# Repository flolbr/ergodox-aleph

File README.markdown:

# Ergodox Aleph 1

Please note that this project uses the nightly version of KiCad (or Kicad 6).

Ergodox [Aleph 1][aleph] is a modification of the [Ergodox Infinity][original].

Major changes include:

* Full Under-Key RGB
* Through-hole diodes for easy soldering
* Replaced the expensive J-Link Needle port with a cheaper J-Link socket
* RGB header for optional underglow
* Added stabiliser holes to 2U keys on thumb cluster
* Replaced discontinued USB ports with new parts

**I've only done the left board so far.**

[aleph]: https://en.wikipedia.org/wiki/Aleph_number
[original]: https://input.club/devices/infinity-ergodox/

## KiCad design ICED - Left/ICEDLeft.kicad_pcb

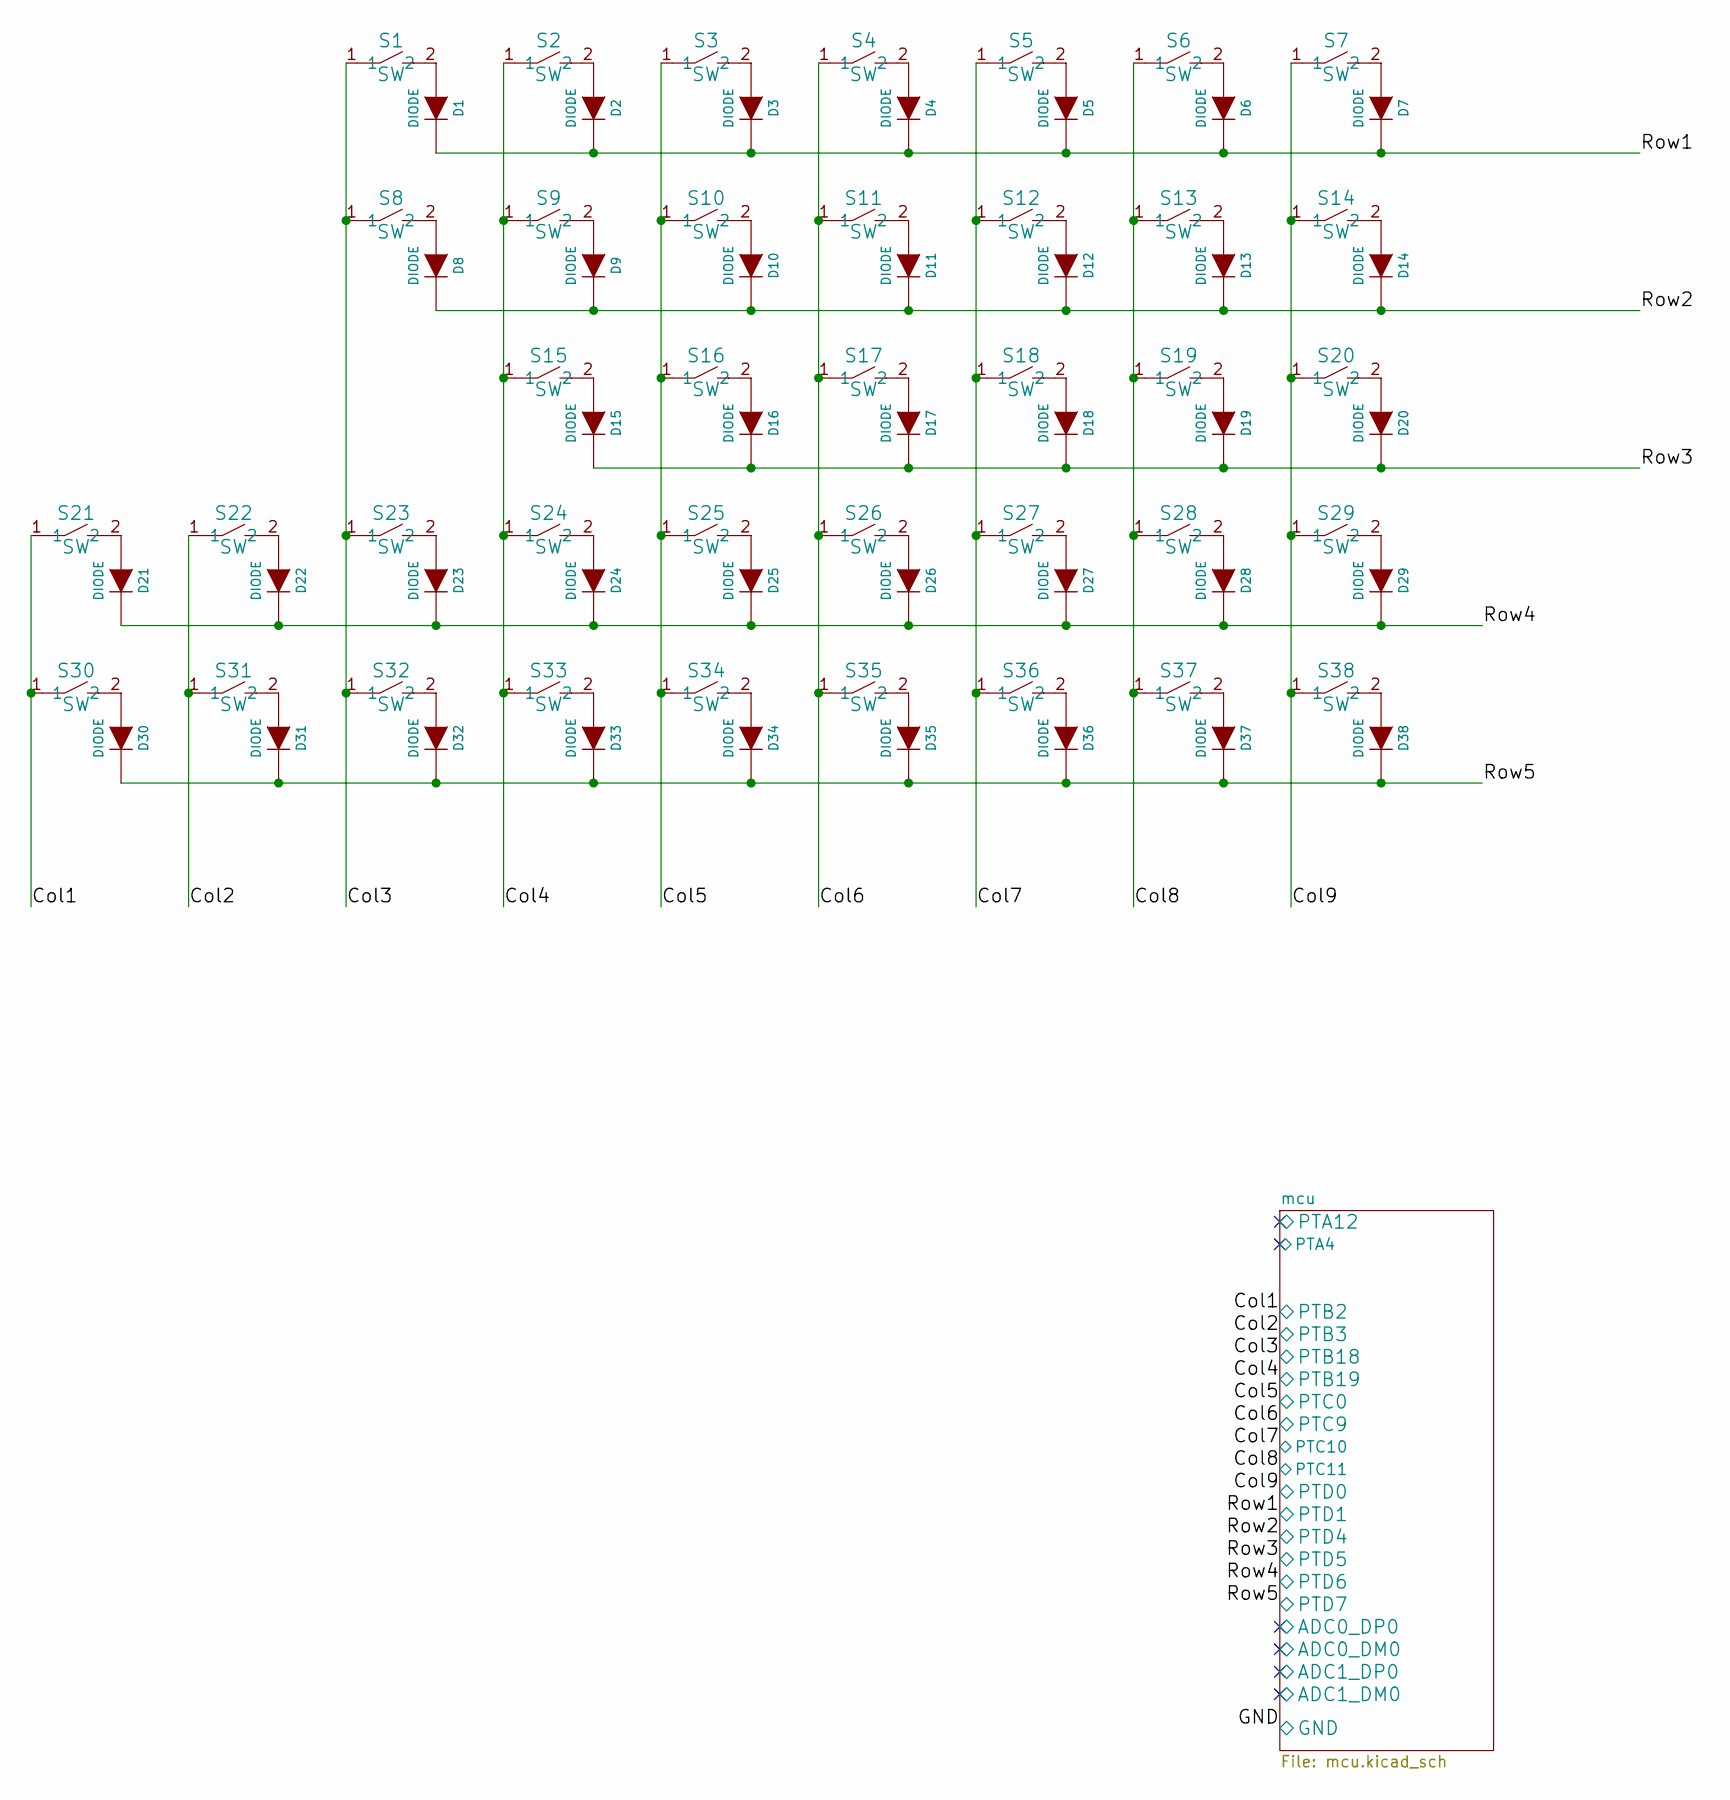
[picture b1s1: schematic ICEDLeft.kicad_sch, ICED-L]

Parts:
D1, D2, D3, D4, D5, D6, D7, D8, D9, D10, D11, D12, D13, D14, D15, D16, D17, D18, D19, D20, D21, D22, D23, D24, D25, D26, D27, D28, D29, D30, D31, D32, D33, D34, D35, D36, D37, D38: DIODE; SOT123-DIODE
S1, S2, S3, S4, S5, S6, S7, S8, S9, S10, S11, S12, S13, S14, S15, S16, S17, S18, S19, S20, S21, S22, S23, S24, S25, S26, S27, S28, S29, S30, S31, S32, S33, S34, S35, S36, S37, S38: SW; SW_Hotswap_Kailh

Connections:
/Col1: S21.1, S30.1; also elsewhere on the board
/Col2: S22.1, S31.1; also elsewhere on the board
/Col3: S1.1, S8.1, S23.1, S32.1; also elsewhere on the board
/Col4: S2.1, S9.1, S15.1, S24.1, S33.1; also elsewhere on the board
/Col5: S3.1, S10.1, S16.1, S25.1, S34.1; also elsewhere on the board
/Col6: S4.1, S11.1, S17.1, S26.1, S35.1; also elsewhere on the board
/Col7: S5.1, S12.1, S18.1, S27.1, S36.1; also elsewhere on the board
/Col8: S6.1, S13.1, S19.1, S28.1, S37.1; also elsewhere on the board
/Col9: S7.1, S14.1, S20.1, S29.1, S38.1; also elsewhere on the board
/Row1: D1.2 (K), D2.2 (K), D3.2 (K), D4.2 (K), D5.2 (K), D6.2 (K), D7.2 (K); also elsewhere on the board
/Row2: D8.2 (K), D9.2 (K), D10.2 (K), D11.2 (K), D12.2 (K), D13.2 (K), D14.2 (K); also elsewhere on the board
/Row3: D15.2 (K), D16.2 (K), D17.2 (K), D18.2 (K), D19.2 (K), D20.2 (K); also elsewhere on the board
/Row4: D21.2 (K), D22.2 (K), D23.2 (K), D24.2 (K), D25.2 (K), D26.2 (K), D27.2 (K), D28.2 (K), D29.2 (K); also elsewhere on the board
/Row5: D30.2 (K), D31.2 (K), D32.2 (K), D33.2 (K), D34.2 (K), D35.2 (K), D36.2 (K), D37.2 (K), D38.2 (K); also elsewhere on the board
unnamed: D1.1 (A), S1.2
unnamed: D2.1 (A), S2.2
unnamed: D3.1 (A), S3.2
unnamed: D4.1 (A), S4.2
unnamed: D5.1 (A), S5.2
unnamed: D6.1 (A), S6.2
unnamed: D7.1 (A), S7.2
unnamed: D8.1 (A), S8.2
unnamed: D9.1 (A), S9.2
unnamed: D10.1 (A), S10.2
unnamed: D11.1 (A), S11.2
unnamed: D12.1 (A), S12.2
unnamed: D13.1 (A), S13.2
unnamed: D14.1 (A), S14.2
unnamed: D15.1 (A), S15.2
unnamed: D16.1 (A), S16.2
unnamed: D17.1 (A), S17.2
unnamed: D18.1 (A), S18.2
unnamed: D19.1 (A), S19.2
unnamed: D20.1 (A), S20.2
unnamed: D21.1 (A), S21.2
unnamed: D22.1 (A), S22.2
unnamed: D23.1 (A), S23.2
unnamed: D24.1 (A), S24.2
unnamed: D25.1 (A), S25.2
unnamed: D26.1 (A), S26.2
unnamed: D27.1 (A), S27.2
unnamed: D28.1 (A), S28.2
unnamed: D29.1 (A), S29.2
unnamed: D30.1 (A), S30.2
unnamed: D31.1 (A), S31.2
unnamed: D32.1 (A), S32.2
unnamed: D33.1 (A), S33.2
unnamed: D34.1 (A), S34.2
unnamed: D35.1 (A), S35.2
unnamed: D36.1 (A), S36.2
unnamed: D37.1 (A), S37.2
unnamed: D38.1 (A), S38.2

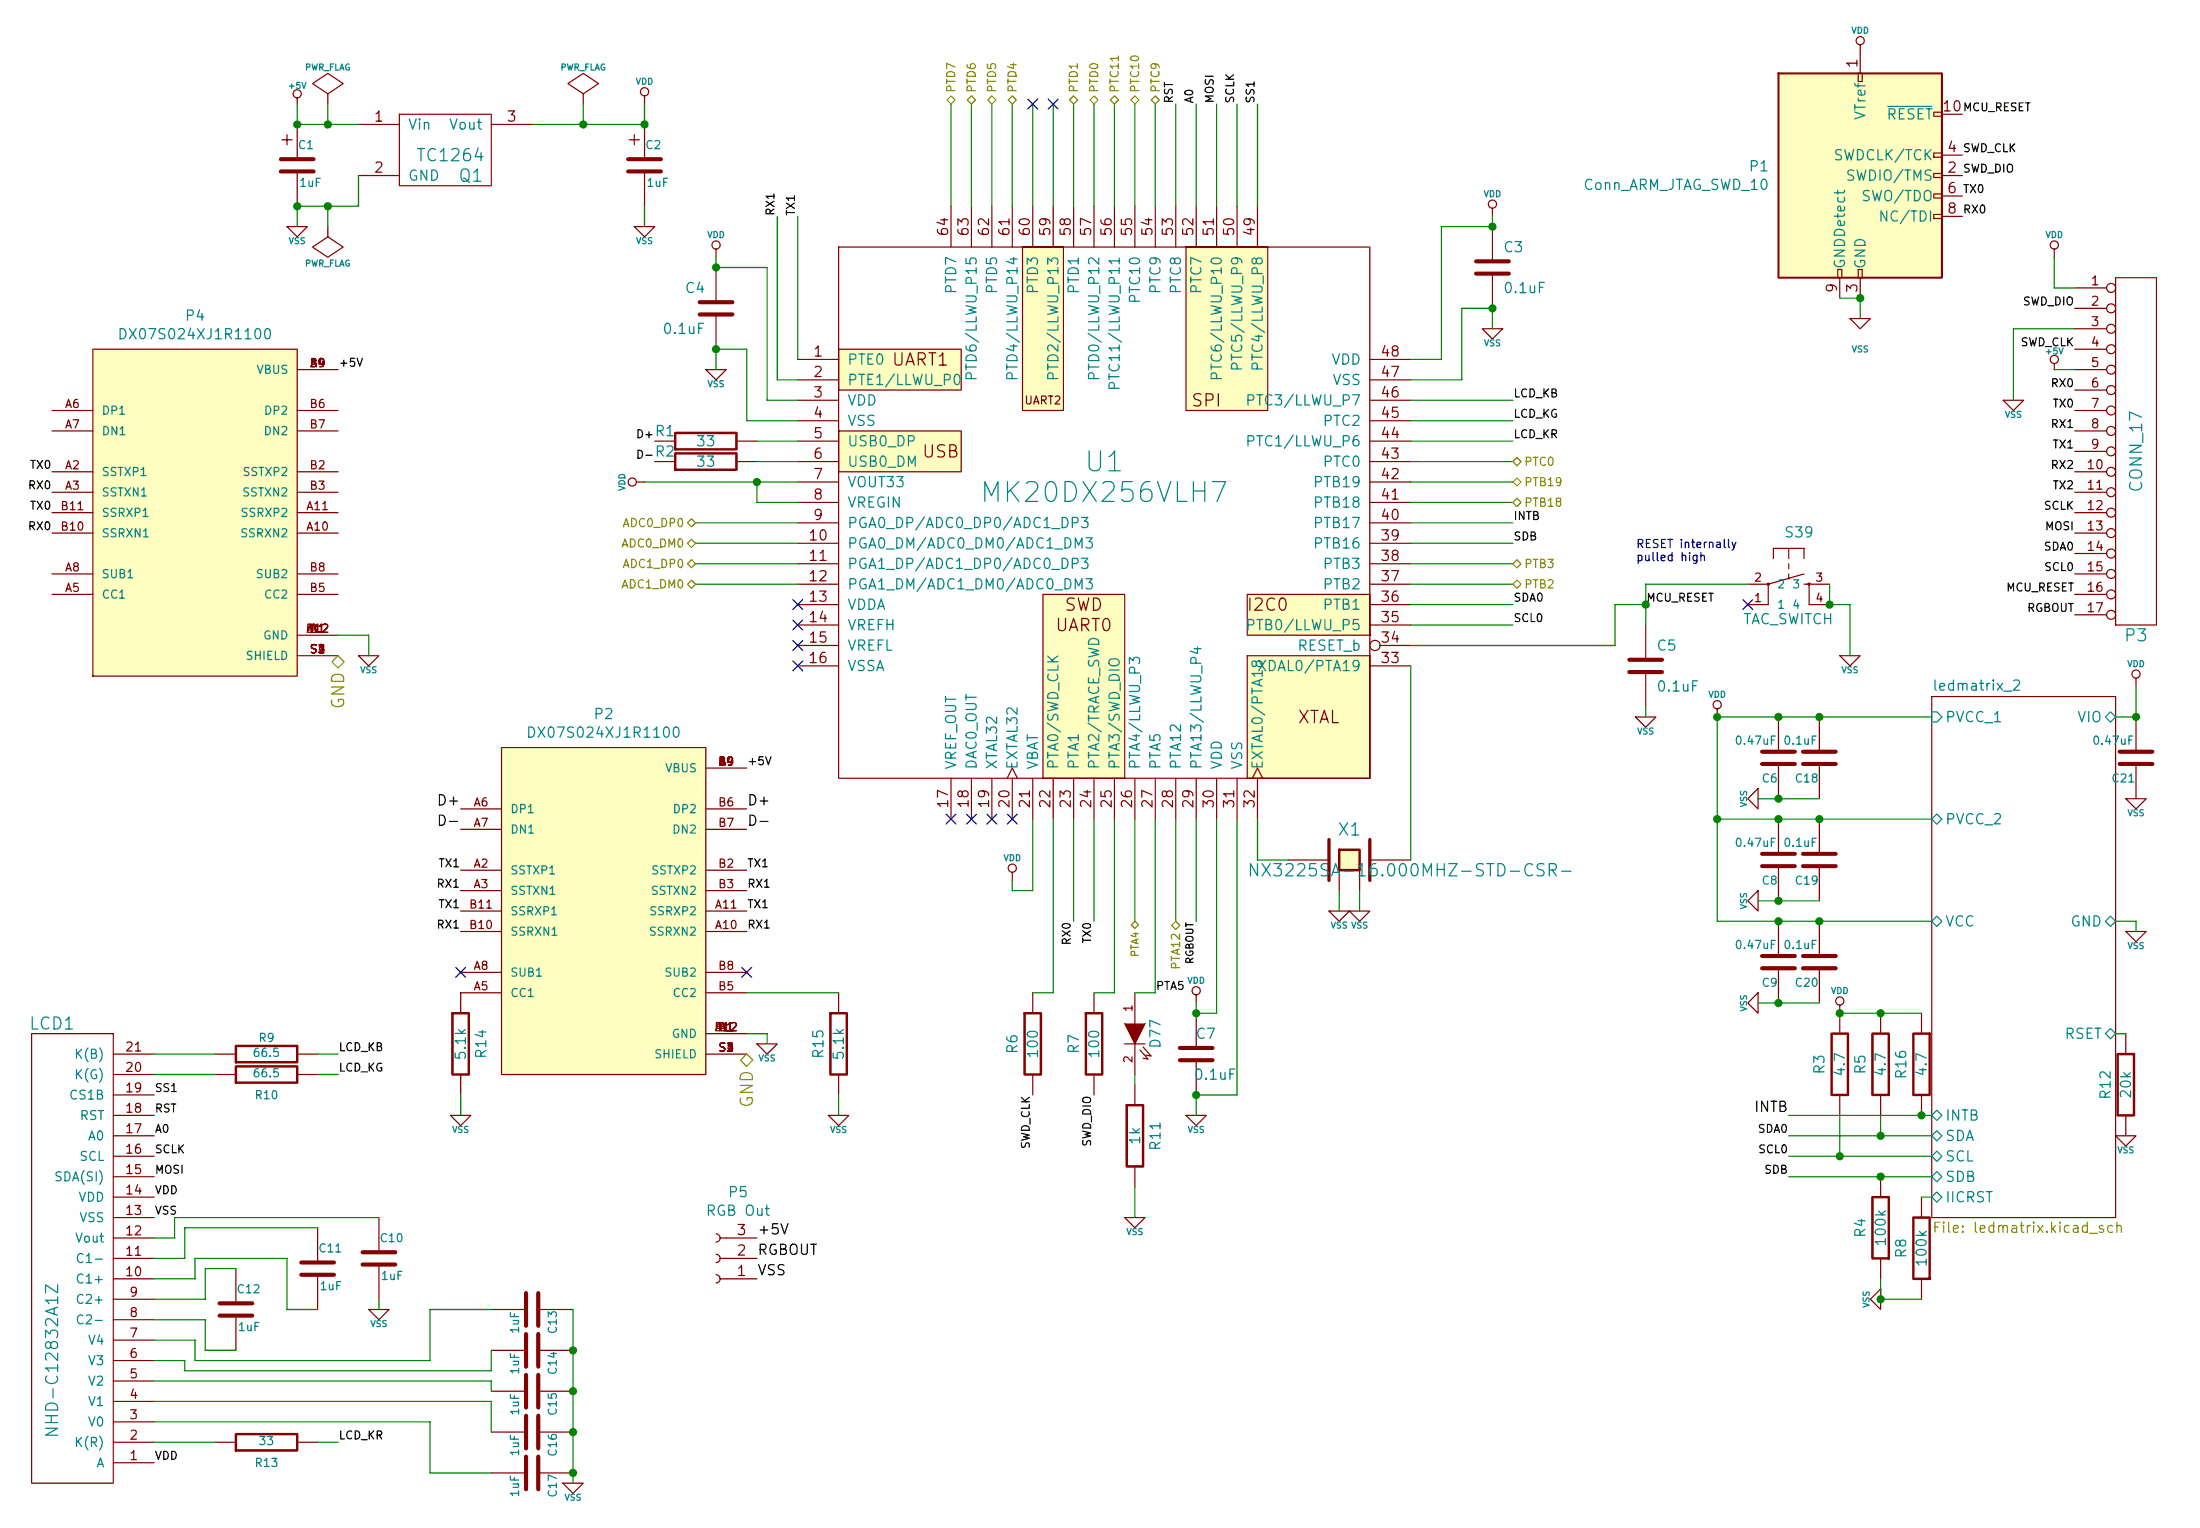
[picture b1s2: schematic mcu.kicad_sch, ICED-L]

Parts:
C1, C2, C10, C11, C12, C13, C14, C15, C16, C17: 1uF; SMD-1005
C3, C4, C5, C7, C18, C19, C20: 0.1uF; SMD-1005
C6, C8, C9, C21: 0.47uF; SMD-1005
D77: LED; LED-0603
LCD1: NHD-C12832A1Z
P1: Conn_ARM_JTAG_SWD_10; SHF-105-01-L-D-TH
P2, P4: DX07S024XJ1R1100; JAE_DX07S024XJ1R1100; PARTREV 1
P3: CONN_17; HEADER_1x17
P5: RGB Out; PinHeader_1x03_P2.54mm_Horizontal
Q1: TC1264; SOT-223
R1, R2, R13: 33; SMD-1005
R3, R5, R16: 4.7; SMD-1005
R4, R8: 100k; SMD-1005
R6, R7: 100; SMD-1005
R9, R10: 66.5; SMD-1005
R11: 1k; SMD-1005
R12: 20k; SMD-1005
R14, R15: 5.1k; SMD-1005
S39: TAC_SWITCH; TACT_5.2x5.2
U1: MK20DX256VLH7; LQFP64
X1: NX3225SA-16.000MHZ-STD-CSR-; NX3225SA

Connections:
+5V: C1.1, P2.A4 (VBUS), P2.A9 (VBUS), P2.B4 (VBUS), P2.B9 (VBUS), P3.5, P4.A4 (VBUS), P4.A9 (VBUS), P4.B4 (VBUS), P4.B9 (VBUS), P5.3, Q1.1 (Vin)
/Col1: U1.37 (PTB2); also elsewhere on the board
/Col2: U1.38 (PTB3); also elsewhere on the board
/Col3: U1.41 (PTB18); also elsewhere on the board
/Col4: U1.42 (PTB19); also elsewhere on the board
/Col5: U1.43 (PTC0); also elsewhere on the board
/Col6: U1.54 (PTC9); also elsewhere on the board
/Col7: U1.55 (PTC10); also elsewhere on the board
/Col8: U1.56 (PTC11/LLWU_P11); also elsewhere on the board
/Col9: U1.57 (PTD0/LLWU_P12); also elsewhere on the board
/GND: P2.S1 (SHIELD), P2.S2 (SHIELD), P2.S3 (SHIELD), P2.S4 (SHIELD), P4.S1 (SHIELD), P4.S2 (SHIELD), P4.S3 (SHIELD), P4.S4 (SHIELD)
/Row1: U1.58 (PTD1); also elsewhere on the board
/Row2: U1.61 (PTD4/LLWU_P14); also elsewhere on the board
/Row3: U1.62 (PTD5); also elsewhere on the board
/Row4: U1.63 (PTD6/LLWU_P15); also elsewhere on the board
/Row5: U1.64 (PTD7); also elsewhere on the board
/mcu/A0: LCD1.17 (A0), U1.52 (PTC7)
/mcu/ADC0_DM0: U1.10 (PGA0_DM/ADC0_DM0/ADC1_DM3)
/mcu/ADC0_DP0: U1.9 (PGA0_DP/ADC0_DP0/ADC1_DP3)
/mcu/ADC1_DM0: U1.12 (PGA1_DM/ADC1_DM0/ADC0_DM3)
/mcu/ADC1_DP0: U1.11 (PGA1_DP/ADC1_DP0/ADC0_DP3)
/mcu/D+: P2.A6 (DP1), P2.B6 (DP2), R1.1
/mcu/D-: P2.A7 (DN1), P2.B7 (DN2), R2.1
/mcu/INTB: R16.2, U1.40 (PTB17); also elsewhere on the board
/mcu/LCD_KB: R9.2, U1.46 (PTC3/LLWU_P7)
/mcu/LCD_KG: R10.2, U1.45 (PTC2)
/mcu/LCD_KR: R13.2, U1.44 (PTC1/LLWU_P6)
/mcu/MCU_RESET: C5.1, P1.10 (~RESET), P3.16, S39.2, U1.34 (RESET_b)
/mcu/MOSI: LCD1.15 (SDA(SI)), P3.13, U1.51 (PTC6/LLWU_P10)
/mcu/PTA4: U1.26 (PTA4/LLWU_P3)
/mcu/PTA5: D77.1 (A), U1.27 (PTA5)
/mcu/PTA12: U1.28 (PTA12)
/mcu/RGBOUT: P3.17, P5.2, U1.29 (PTA13/LLWU_P4)
/mcu/RST: LCD1.18 (RST), U1.53 (PTC8)
/mcu/RX0: P1.8 (NC/TDI), P3.6, P4.A3 (SSTXN1), P4.B10 (SSRXN1), U1.23 (PTA1)
/mcu/RX1: P2.A3 (SSTXN1), P2.A10 (SSRXN2), P2.B3 (SSTXN2), P2.B10 (SSRXN1), P3.8, U1.2 (PTE1/LLWU_P0)
/mcu/RX2: P3.10
/mcu/SCL0: P3.15, R3.1, U1.35 (PTB0/LLWU_P5); also elsewhere on the board
/mcu/SCLK: LCD1.16 (SCL), P3.12, U1.50 (PTC5/LLWU_P9)
/mcu/SDA0: P3.14, R5.1, U1.36 (PTB1); also elsewhere on the board
/mcu/SDB: R4.2, U1.39 (PTB16); also elsewhere on the board
/mcu/SS1: LCD1.19 (CS1B), U1.49 (PTC4/LLWU_P8)
/mcu/SWD_CLK: P1.4 (SWDCLK/TCK), P3.4, R6.2
/mcu/SWD_DIO: P1.2 (SWDIO/TMS), P3.2, R7.2
/mcu/TX0: P1.6 (SWO/TDO), P3.7, P4.A2 (SSTXP1), P4.B11 (SSRXP1), U1.24 (PTA2/TRACE_SWD)
/mcu/TX1: P2.A2 (SSTXP1), P2.A11 (SSRXP2), P2.B2 (SSTXP2), P2.B11 (SSRXP1), P3.9, U1.1 (PTE0)
/mcu/TX2: P3.11
/mcu/ledmatrix_2/IICRST: R8.2; also elsewhere on the board
/mcu/ledmatrix_2/RSET: R12.1; also elsewhere on the board
unnamed: C10.1, LCD1.12 (Vout)
unnamed: C11.1, LCD1.11 (C1-)
unnamed: C11.2, LCD1.10 (C1+)
unnamed: C12.1, LCD1.9 (C2+)
unnamed: C12.2, LCD1.8 (C2-)
unnamed: C13.2, LCD1.7 (V4)
unnamed: C14.2, LCD1.6 (V3)
unnamed: C15.2, LCD1.5 (V2)
unnamed: C16.2, LCD1.4 (V1)
unnamed: C17.2, LCD1.3 (V0)
unnamed: D77.2 (K), R11.1
unnamed: LCD1.2 (K(R)), R13.1
unnamed: LCD1.20 (K(G)), R10.1
unnamed: LCD1.21 (K(B)), R9.1
unnamed: R1.2, U1.5 (USB0_DP)
unnamed: R2.2, U1.6 (USB0_DM)
unnamed: R6.1, U1.22 (PTA0/SWD_CLK)
unnamed: R7.1, U1.25 (PTA3/SWD_DIO)
unnamed: P2.A5 (CC1), R14.1
unnamed: P2.B5 (CC2), R15.1
unnamed: U1.32 (EXTAL0/PTA18), X1.1
unnamed: U1.33 (XDAL0/PTA19), X1.3
VDD: C2.1, C3.1, C4.1, C6.2, C7.1, C8.2, C9.2, C18.2, C19.2, C20.2, C21.2, LCD1.1 (A), LCD1.14 (VDD), P1.1 (VTref), P3.1, Q1.3 (Vout), R3.2, R5.2, R16.1, U1.3 (VDD), U1.7 (VOUT33), U1.8 (VREGIN), U1.21 (VBAT), U1.30 (VDD), U1.48 (VDD); also elsewhere on the board
VSS: C1.2, C2.2, C3.2, C4.2, C5.2, C6.1, C7.2, C8.1, C9.1, C10.2, C13.1, C14.1, C15.1, C16.1, C17.1, C18.1, C19.1, C20.1, C21.1, LCD1.13 (VSS), P1.3 (GND), P1.5 (GND), P1.9 (GNDDetect), P2.A1 (GND), P2.A12 (GND), P2.B1 (GND), P2.B12 (GND), P3.3, P4.A1 (GND), P4.A12 (GND), P4.B1 (GND), P4.B12 (GND), P5.1, Q1.2 (GND), R4.1, R8.1, R11.2, R12.2, R14.2, R15.2, S39.3, S39.4, U1.4 (VSS), U1.31 (VSS), U1.47 (VSS), X1.2, X1.4; also elsewhere on the board

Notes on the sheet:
RESET internally pulled high

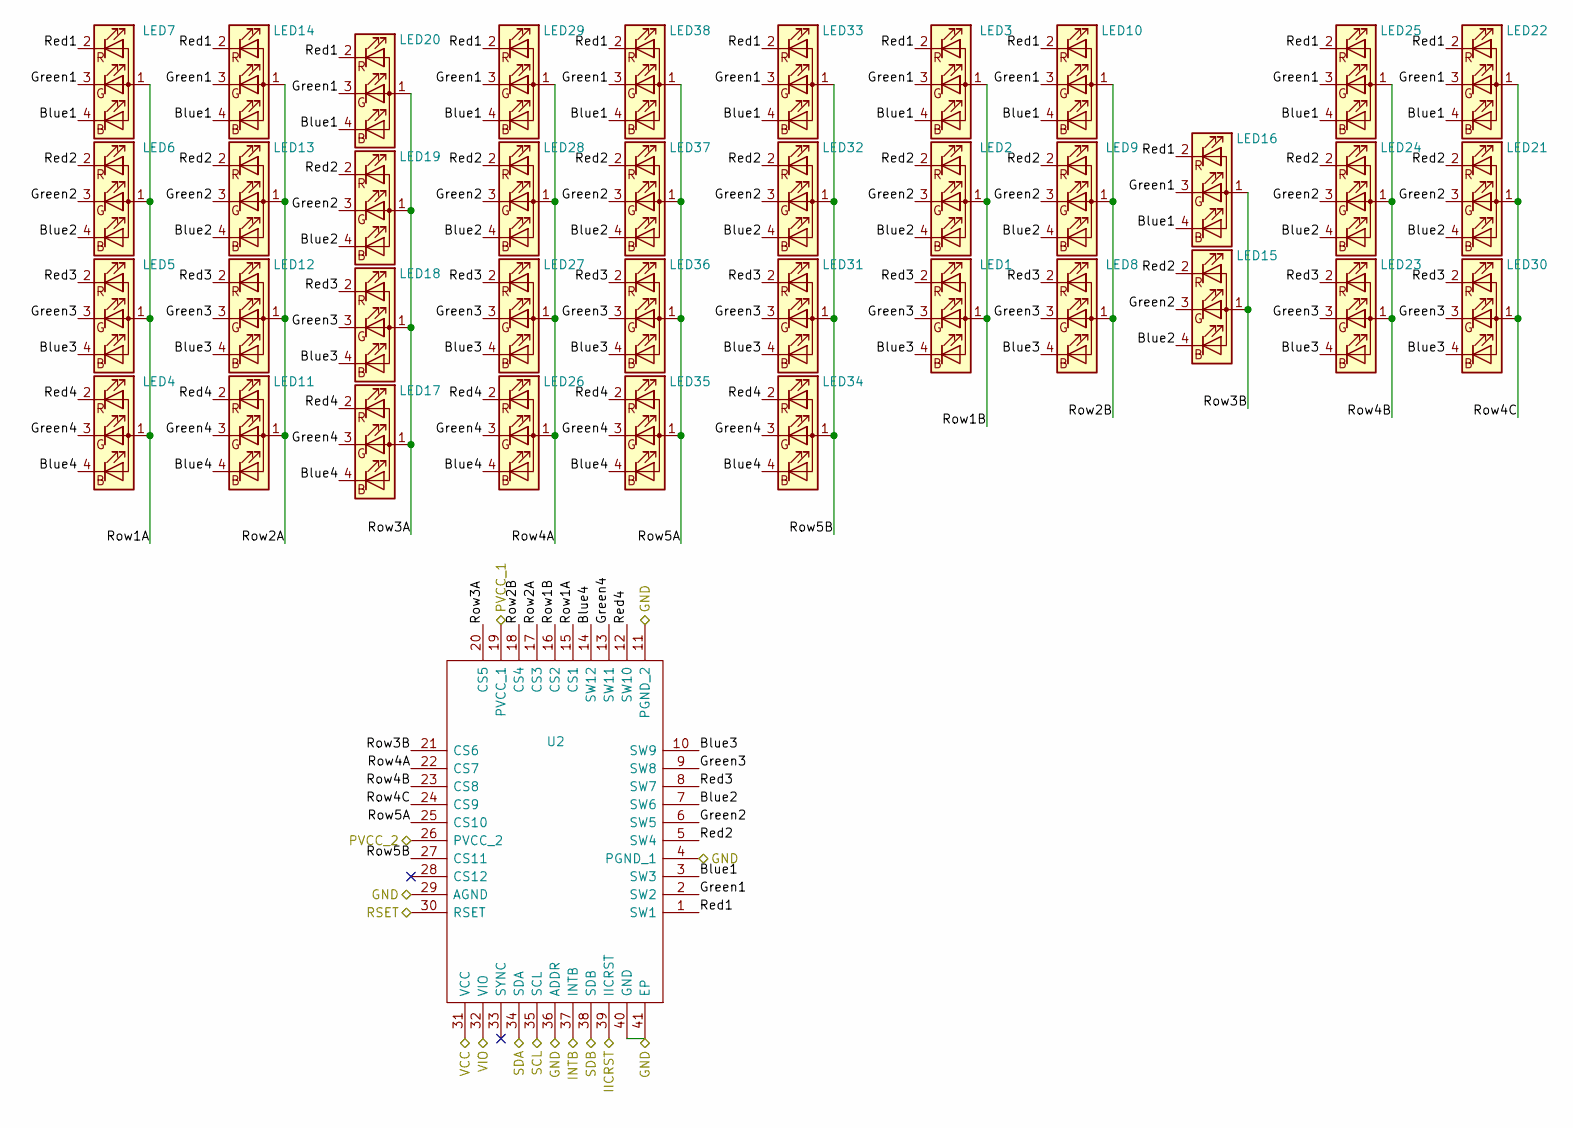
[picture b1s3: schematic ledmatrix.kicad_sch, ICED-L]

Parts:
LED1, LED2, LED3, LED4, LED5, LED6, LED7, LED8, LED9, LED10, LED11, LED12, LED13, LED14, LED15, LED16, LED17, LED18, LED19, LED20, LED21, LED22, LED23, LED24, LED25, LED26, LED27, LED28, LED29, LED30, LED31, LED32, LED33, LED34, LED35, LED36, LED37, LED38: RGB_0606; 0606
U2: IS31FL3737-QFLS4-TR; QFN40P500X500X80-41N-D; Manufacturer_Part_Number IS31FL3737-QFLS4-TR; Mouser Part Number 870-31FL3737QFLS4TR

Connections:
/mcu/INTB: U2.37 (INTB); also elsewhere on the board
/mcu/SCL0: U2.35 (SCL); also elsewhere on the board
/mcu/SDA0: U2.34 (SDA); also elsewhere on the board
/mcu/SDB: U2.38 (SDB); also elsewhere on the board
/mcu/ledmatrix_2/Blue1: LED3.4 (BK), LED7.4 (BK), LED10.4 (BK), LED14.4 (BK), LED16.4 (BK), LED20.4 (BK), LED22.4 (BK), LED25.4 (BK), LED29.4 (BK), LED33.4 (BK), LED38.4 (BK), U2.3 (SW3)
/mcu/ledmatrix_2/Blue2: LED2.4 (BK), LED6.4 (BK), LED9.4 (BK), LED13.4 (BK), LED15.4 (BK), LED19.4 (BK), LED21.4 (BK), LED24.4 (BK), LED28.4 (BK), LED32.4 (BK), LED37.4 (BK), U2.7 (SW6)
/mcu/ledmatrix_2/Blue3: LED1.4 (BK), LED5.4 (BK), LED8.4 (BK), LED12.4 (BK), LED18.4 (BK), LED23.4 (BK), LED27.4 (BK), LED30.4 (BK), LED31.4 (BK), LED36.4 (BK), U2.10 (SW9)
/mcu/ledmatrix_2/Blue4: LED4.4 (BK), LED11.4 (BK), LED17.4 (BK), LED26.4 (BK), LED34.4 (BK), LED35.4 (BK), U2.14 (SW12)
/mcu/ledmatrix_2/Green1: LED3.3 (GK), LED7.3 (GK), LED10.3 (GK), LED14.3 (GK), LED16.3 (GK), LED20.3 (GK), LED22.3 (GK), LED25.3 (GK), LED29.3 (GK), LED33.3 (GK), LED38.3 (GK), U2.2 (SW2)
/mcu/ledmatrix_2/Green2: LED2.3 (GK), LED6.3 (GK), LED9.3 (GK), LED13.3 (GK), LED15.3 (GK), LED19.3 (GK), LED21.3 (GK), LED24.3 (GK), LED28.3 (GK), LED32.3 (GK), LED37.3 (GK), U2.6 (SW5)
/mcu/ledmatrix_2/Green3: LED1.3 (GK), LED5.3 (GK), LED8.3 (GK), LED12.3 (GK), LED18.3 (GK), LED23.3 (GK), LED27.3 (GK), LED30.3 (GK), LED31.3 (GK), LED36.3 (GK), U2.9 (SW8)
/mcu/ledmatrix_2/Green4: LED4.3 (GK), LED11.3 (GK), LED17.3 (GK), LED26.3 (GK), LED34.3 (GK), LED35.3 (GK), U2.13 (SW11)
/mcu/ledmatrix_2/IICRST: U2.39 (IICRST); also elsewhere on the board
/mcu/ledmatrix_2/RSET: U2.30 (RSET); also elsewhere on the board
/mcu/ledmatrix_2/Red1: LED3.2 (RK), LED7.2 (RK), LED10.2 (RK), LED14.2 (RK), LED16.2 (RK), LED20.2 (RK), LED22.2 (RK), LED25.2 (RK), LED29.2 (RK), LED33.2 (RK), LED38.2 (RK), U2.1 (SW1)
/mcu/ledmatrix_2/Red2: LED2.2 (RK), LED6.2 (RK), LED9.2 (RK), LED13.2 (RK), LED15.2 (RK), LED19.2 (RK), LED21.2 (RK), LED24.2 (RK), LED28.2 (RK), LED32.2 (RK), LED37.2 (RK), U2.5 (SW4)
/mcu/ledmatrix_2/Red3: LED1.2 (RK), LED5.2 (RK), LED8.2 (RK), LED12.2 (RK), LED18.2 (RK), LED23.2 (RK), LED27.2 (RK), LED30.2 (RK), LED31.2 (RK), LED36.2 (RK), U2.8 (SW7)
/mcu/ledmatrix_2/Red4: LED4.2 (RK), LED11.2 (RK), LED17.2 (RK), LED26.2 (RK), LED34.2 (RK), LED35.2 (RK), U2.12 (SW10)
/mcu/ledmatrix_2/Row1A: LED4.1 (A), LED5.1 (A), LED6.1 (A), LED7.1 (A), U2.15 (CS1)
/mcu/ledmatrix_2/Row1B: LED1.1 (A), LED2.1 (A), LED3.1 (A), U2.16 (CS2)
/mcu/ledmatrix_2/Row2A: LED11.1 (A), LED12.1 (A), LED13.1 (A), LED14.1 (A), U2.17 (CS3)
/mcu/ledmatrix_2/Row2B: LED8.1 (A), LED9.1 (A), LED10.1 (A), U2.18 (CS4)
/mcu/ledmatrix_2/Row3A: LED17.1 (A), LED18.1 (A), LED19.1 (A), LED20.1 (A), U2.20 (CS5)
/mcu/ledmatrix_2/Row3B: LED15.1 (A), LED16.1 (A), U2.21 (CS6)
/mcu/ledmatrix_2/Row4A: LED26.1 (A), LED27.1 (A), LED28.1 (A), LED29.1 (A), U2.22 (CS7)
/mcu/ledmatrix_2/Row4B: LED23.1 (A), LED24.1 (A), LED25.1 (A), U2.23 (CS8)
/mcu/ledmatrix_2/Row4C: LED21.1 (A), LED22.1 (A), LED30.1 (A), U2.24 (CS9)
/mcu/ledmatrix_2/Row5A: LED35.1 (A), LED36.1 (A), LED37.1 (A), LED38.1 (A), U2.25 (CS10)
/mcu/ledmatrix_2/Row5B: LED31.1 (A), LED32.1 (A), LED33.1 (A), LED34.1 (A), U2.27 (CS11)
VDD: U2.19 (PVCC_1), U2.26 (PVCC_2), U2.31 (VCC), U2.32 (VIO); also elsewhere on the board
VSS: U2.4 (PGND_1), U2.11 (PGND_2), U2.29 (AGND), U2.36 (ADDR), U2.40 (GND), U2.41 (EP); also elsewhere on the board

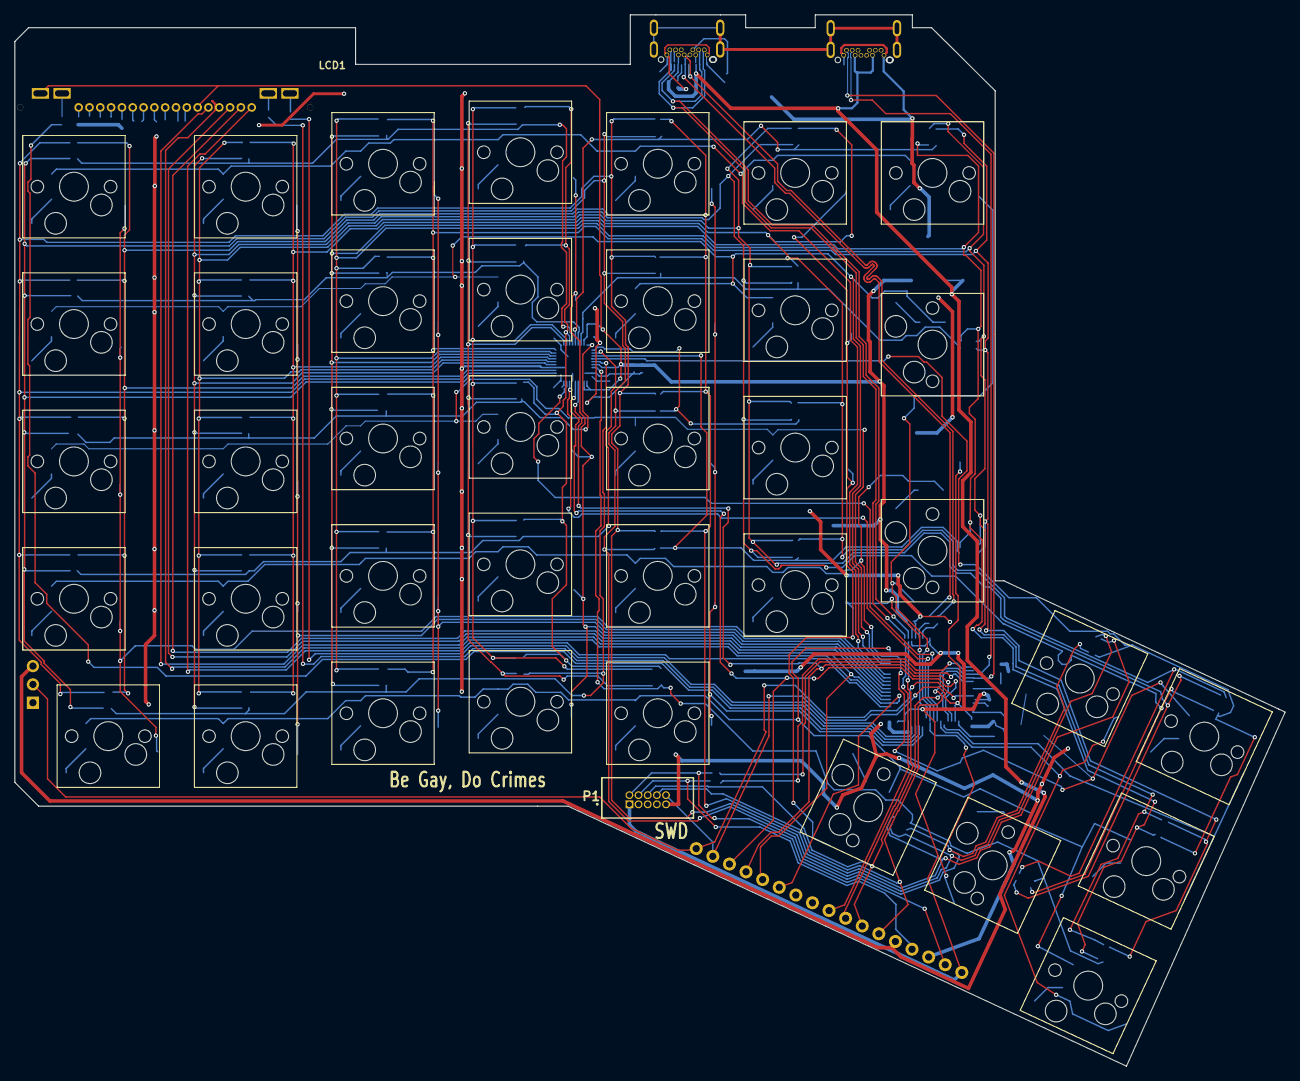
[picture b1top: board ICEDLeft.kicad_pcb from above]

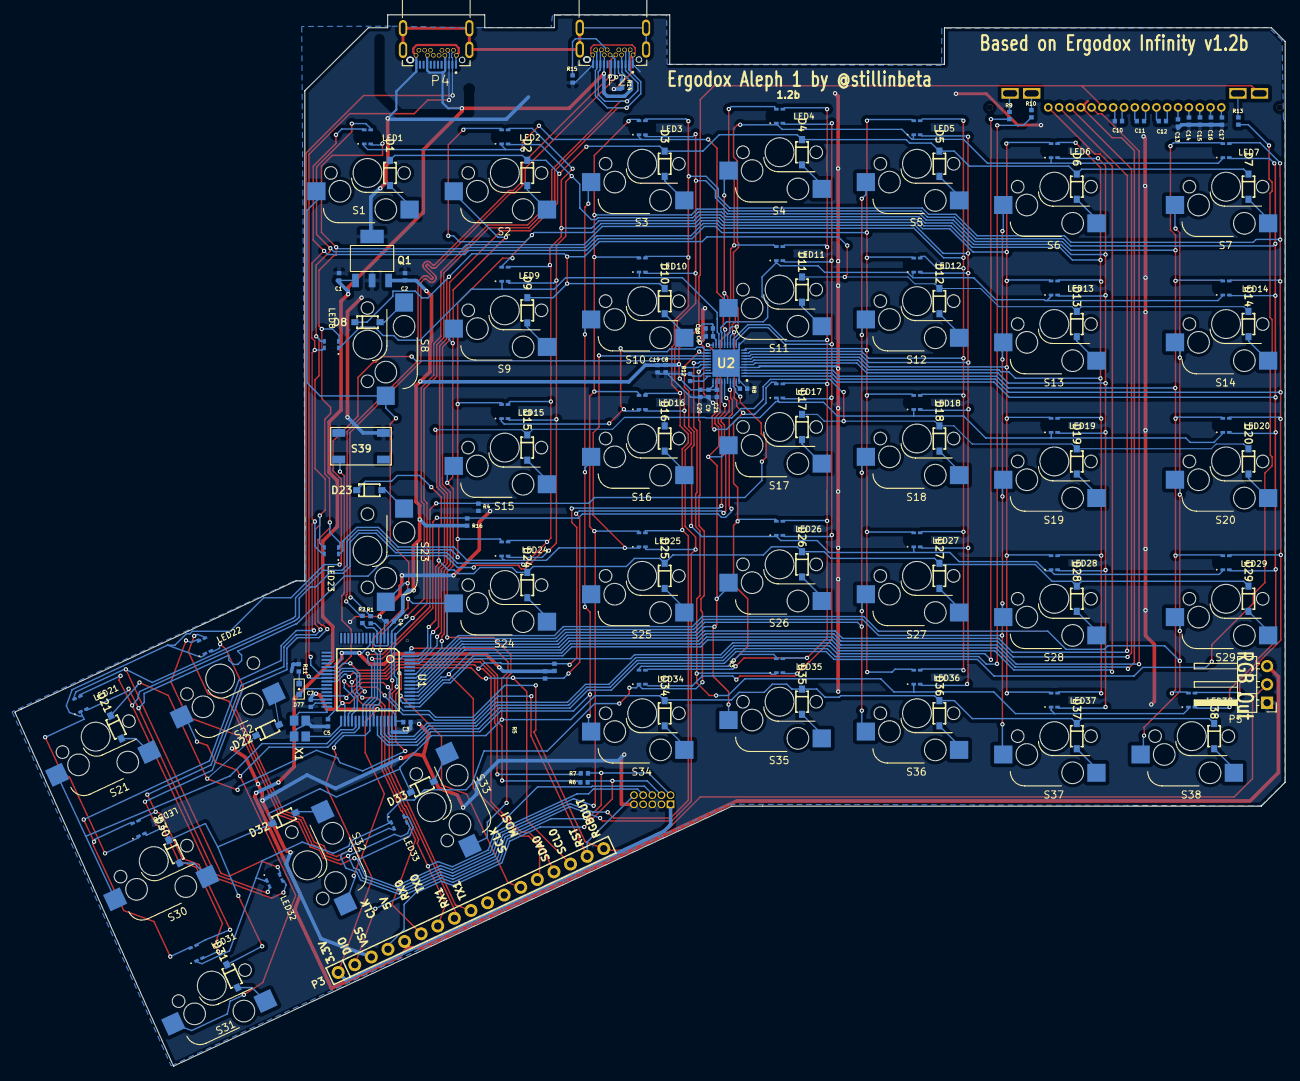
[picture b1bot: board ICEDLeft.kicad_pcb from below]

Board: 2 copper layers, 176.2 x 145.8 mm, 163 parts (123 on the bottom side), 126 nets.

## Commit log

2021-03-15 RGB LEDs
2021-03-16 Finished laying out components
2021-03-17 routed and DRC'd
2021-03-18 RGB headers and finishing touches!
2021-03-18 Remove other projects
2021-03-18 more final tweaks
2021-03-19 Ignore the Gerbers
2021-03-19 LED Matrix Connected
2021-03-19 Footprints placed
2021-03-20 Added support caps
2021-03-20 left 50% routed
2021-03-20 Routed new USB ports
2021-03-20 Cleaned up DRC issues
2021-03-21 More routing
2021-03-21 Most non-thumb routing finished
2021-03-22 Routed and DRC passes
2021-03-22 stabilizer logs
2021-03-22 re-added RGBOUT
2021-03-22 tweaks and cleanup
2021-03-22 even more final tweaks
2021-03-23 Kailh hotswaps and ground plane
2021-03-24 0606 LEDs
2021-03-28 Routed correctly
2021-03-28 move RGB header to left side
2021-03-28 missing USB C header
2021-03-30 are you not done tweaking
2021-03-30 finalised
2021-04-02 set jcl design constraints
2021-04-02 No DRC violations!
2021-04-03 Routing WIP
2021-04-04 Routing WIP2
2021-04-05 50 nets to go
2021-04-05 Migrate schematics and more routing
2021-04-05 --amend
2021-04-05 mostly routed
2021-04-05 Second Revision Finalised
2021-04-05 Add Kicad 6 note
2021-04-05 Reorganized footprints
2021-04-05 Updated schematic PDF
2021-04-05 Removed unused net file
2021-04-05 Replaced BOM
2021-04-11 freecad case wip
2021-04-12 more case WIP
2021-04-16 even more case WIP
2021-05-03 Add some 3D models
2021-05-03 tweak values
2021-05-05 nicely filleted topcase
2021-09-25 Upgrade project + Right changes
    - Replace MXALPS sockets by Kailh Hot-swaps
    - Replace the LED controller
2021-09-25 Place all LEDs with their switch + resistors
2021-09-26 LED orientation and start routing around main mcu
2021-09-26 Change J-Link connector
2021-09-27 Left: Revert to SMD diodes
2021-09-28 Left: position and start reouting SMD diodes
2021-09-29 Left: more routing
